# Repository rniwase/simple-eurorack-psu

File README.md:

# simple-eurorack-psu
An 4-port PSU for Eurorack module.

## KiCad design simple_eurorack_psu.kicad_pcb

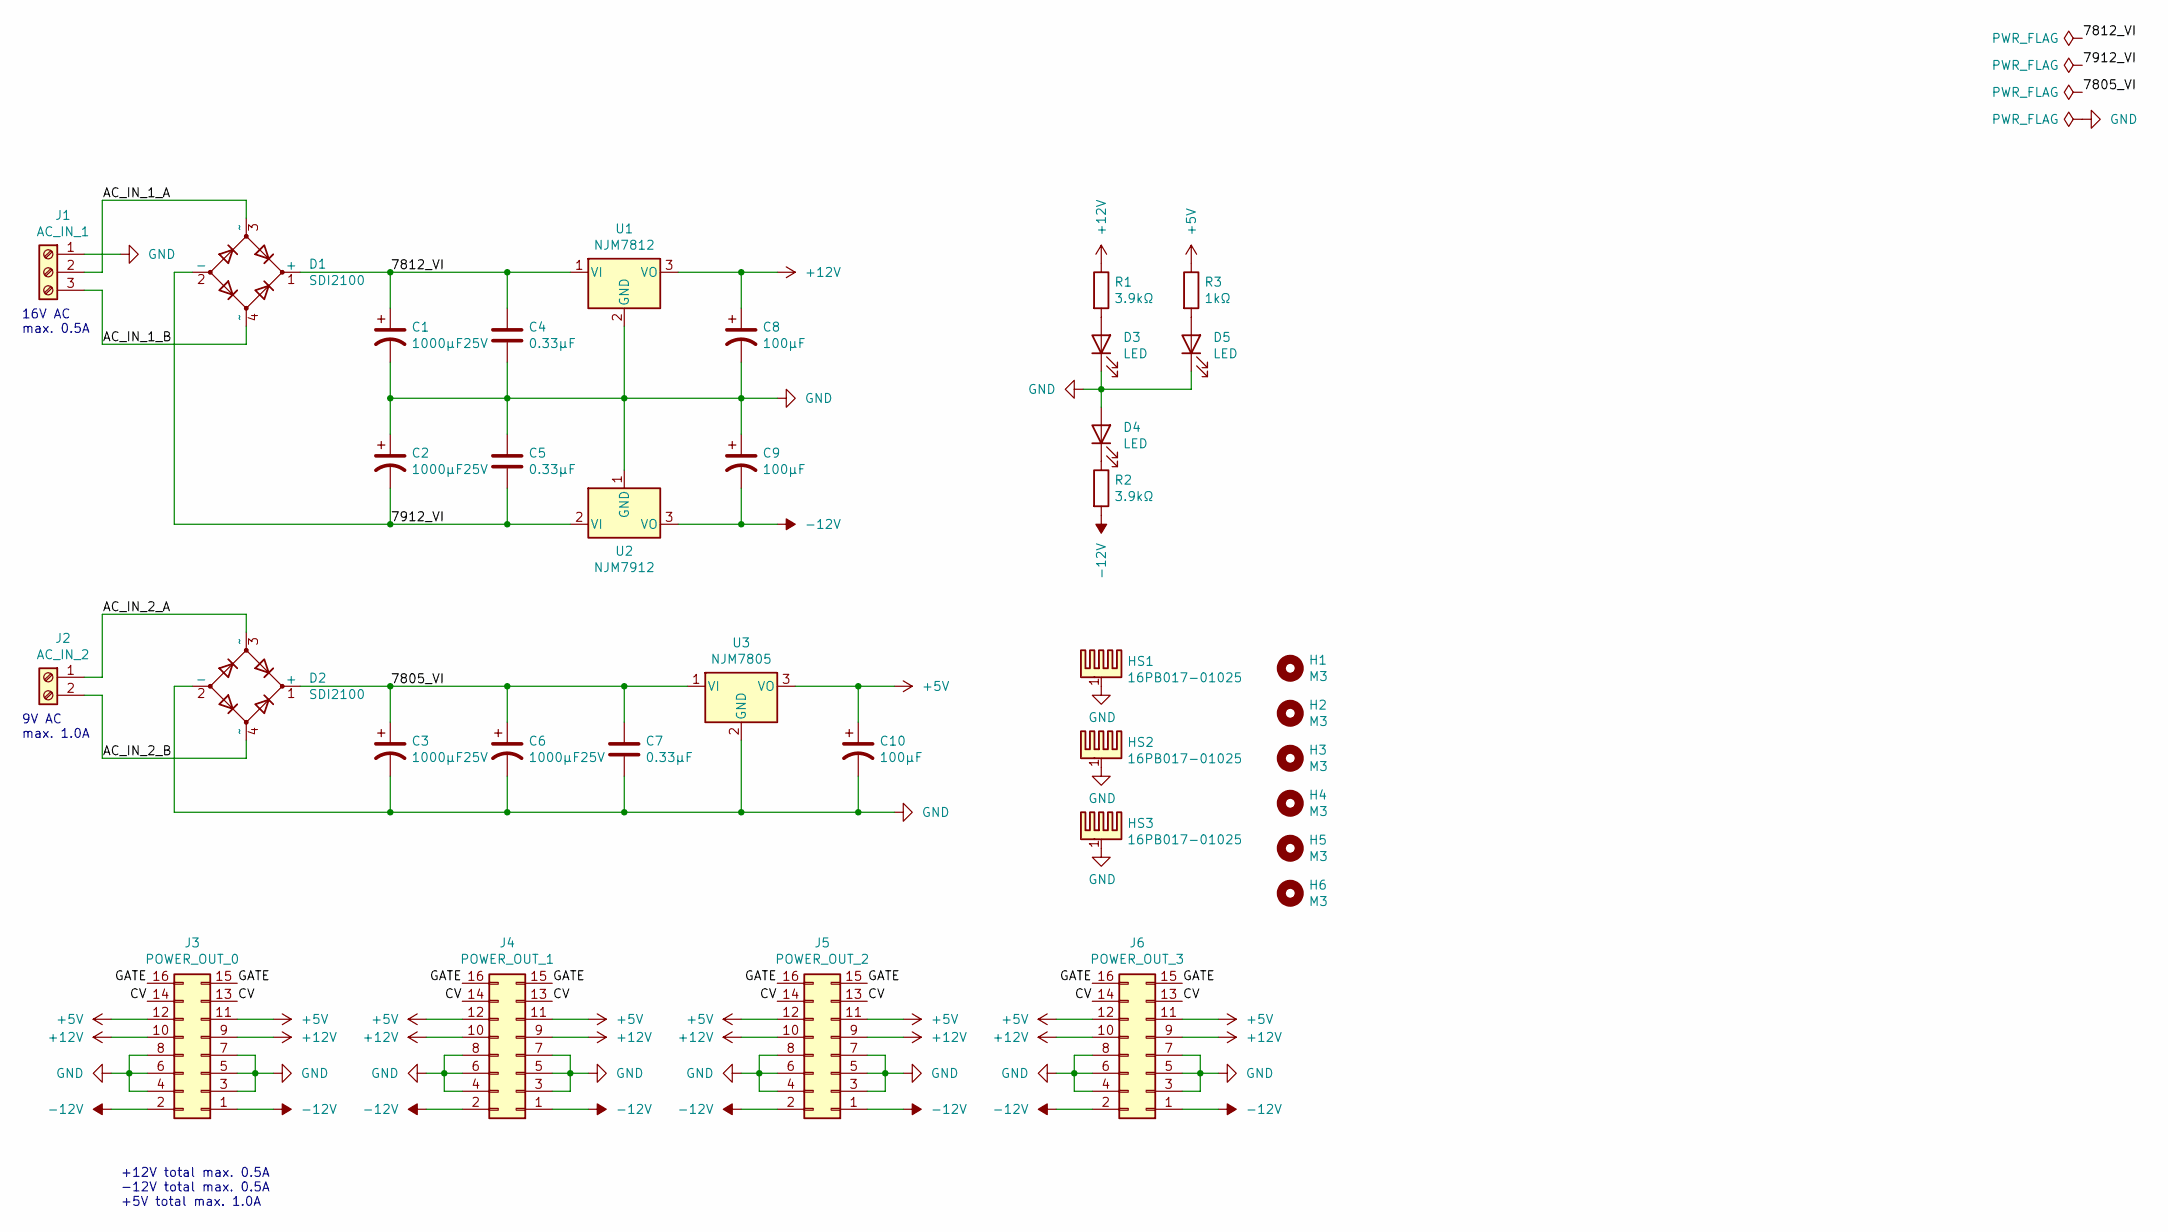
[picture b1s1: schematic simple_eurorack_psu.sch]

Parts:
C1, C2, C3, C6: 1000μF25V; CP_Radial_D12.5mm_P5.00mm
C4, C5, C7: 0.33μF; C_Disc_D3.4mm_W2.1mm_P2.50mm
C8, C9, C10: 100μF; CP_Radial_D6.3mm_P2.50mm
D1, D2: SDI2100
D3, D4, D5: LED; LED_D3.0mm
H1, H2, H3, H4, H5, H6: M3; MountingHole_3.2mm_M3
HS1, HS2, HS3: 16PB017-01025
J1: AC_IN_1; PhoenixContact_MSTBA_2,5_3-G-5,08_1x03_P5.08mm_Horizontal
J2: AC_IN_2; PhoenixContact_MSTBA_2,5_2-G-5,08_1x02_P5.08mm_Horizontal
J3: POWER_OUT_0; IDC-Header_2x08_P2.54mm_Vertical
J4: POWER_OUT_1; IDC-Header_2x08_P2.54mm_Vertical
J5: POWER_OUT_2; IDC-Header_2x08_P2.54mm_Vertical
J6: POWER_OUT_3; IDC-Header_2x08_P2.54mm_Vertical
R1, R2: 3.9kΩ; R_Axial_DIN0207_L6.3mm_D2.5mm_P2.54mm_Vertical
R3: 1kΩ; R_Axial_DIN0207_L6.3mm_D2.5mm_P2.54mm_Vertical
U1: NJM7812; TO-220-3_Vertical
U2: NJM7912; TO-220-3_Vertical
U3: NJM7805; TO-220-3_Vertical

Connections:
+5V: C10.1, J3.11, J3.12, J4.11, J4.12, J5.11, J5.12, J6.11, J6.12, R3.1, U3.3 (VO)
+12V: C8.1, J3.9, J3.10, J4.9, J4.10, J5.9, J5.10, J6.9, J6.10, R1.1, U1.3 (VO)
-12V: C9.2, J3.1, J3.2, J4.1, J4.2, J5.1, J5.2, J6.1, J6.2, R2.2, U2.3 (VO)
/7805_VI: C3.1, C6.1, C7.1, D2.1 (+), U3.1 (VI)
/7812_VI: C1.1, C4.1, D1.1 (+), U1.1 (VI)
/7912_VI: C2.2, C5.2, D1.2 (-), U2.2 (VI)
/AC_IN_1_A: D1.3 (~~), J1.2
/AC_IN_1_B: D1.4 (~~), J1.3
/AC_IN_2_A: D2.3 (~~), J2.1
/AC_IN_2_B: D2.4 (~~), J2.2
/CV: J3.13, J3.14, J4.13, J4.14, J5.13, J5.14, J6.13, J6.14
/GATE: J3.15, J3.16, J4.15, J4.16, J5.15, J5.16, J6.15, J6.16
GND: C1.2, C2.1, C3.2, C4.2, C5.1, C6.2, C7.2, C8.2, C9.1, C10.2, D2.2 (-), D3.1 (K), D4.2 (A), D5.1 (K), HS1.1, HS2.1, HS3.1, J1.1, J3.3, J3.4, J3.5, J3.6, J3.7, J3.8, J4.3, J4.4, J4.5, J4.6, J4.7, J4.8, J5.3, J5.4, J5.5, J5.6, J5.7, J5.8, J6.3, J6.4, J6.5, J6.6, J6.7, J6.8, U1.2 (GND), U2.1 (GND), U3.2 (GND)
unnamed: D3.2 (A), R1.2
unnamed: D4.1 (K), R2.1
unnamed: D5.2 (A), R3.2

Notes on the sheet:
16V AC max. 0.5A
9V AC max. 1.0A
+12V total max. 0.5A -12V total max. 0.5A +5V total max. 1.0A

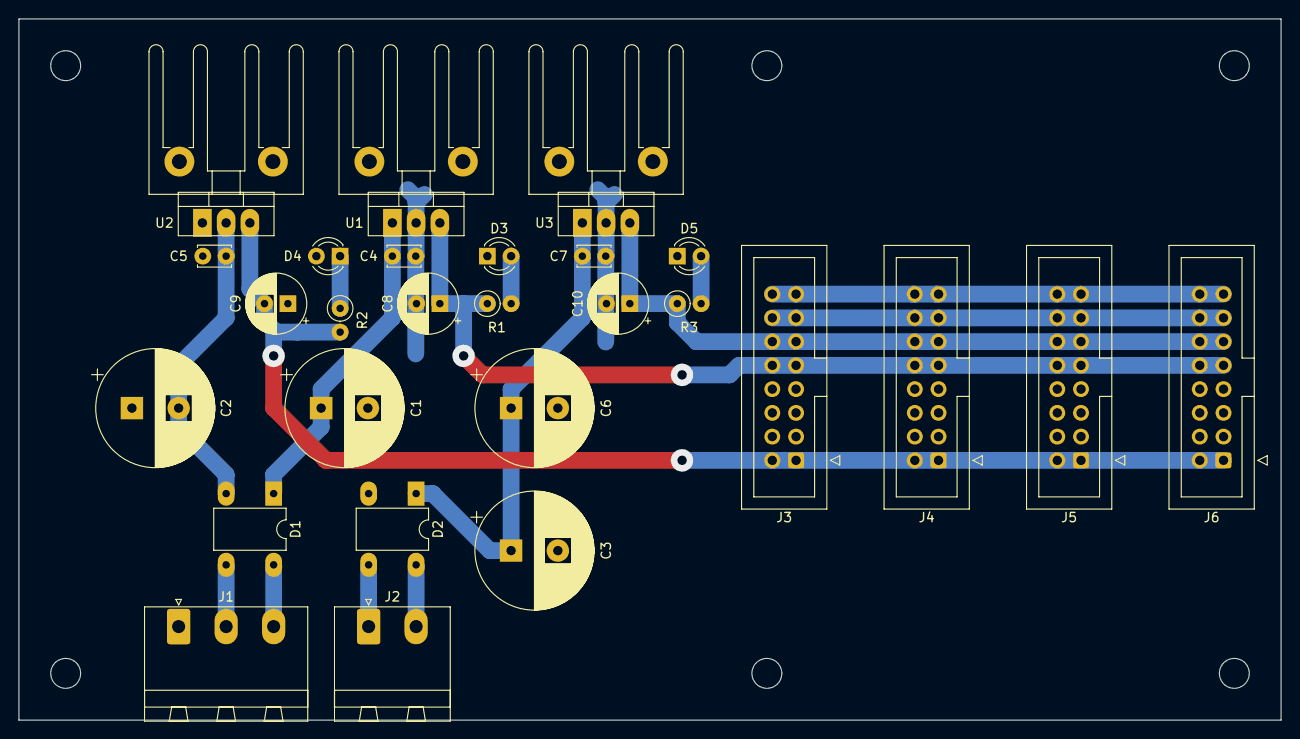
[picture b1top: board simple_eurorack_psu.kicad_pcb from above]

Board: 2 copper layers, 135.0 x 75.0 mm, 36 parts (0 on the bottom side), 16 nets.

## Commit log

2020-10-23 reposition capacitors
2020-12-11 add .gitattributes
